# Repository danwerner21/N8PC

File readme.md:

# N8PC
The N8PC is a Z180 ATX format board with 512K RAM, 512K of ROM, that supports RomWBW and is compatible enough with MSX to run many games.  It supports a 82c42 PS2 keyboard controller, a TMS9918 emulator (either Pico9918, F19A or Tang Nano) for 80 column video output, a Ay-3-8910 PSG for sound, a 6242 RTC, ATARI/MSX style Joysticks (2 button supported) and 6 ISAish slots.  This computer is supported by the RomWBW ecosystem with full CP/M OS Support.

Note that 9.218Mhz is the recommended system clock speed for this system.  

## BUGS
```
V1.1 version PCBs have not been tested yet.

Bodges for V1.0 of Board
U33 Cut Pin 3 traces on both Top and Bottom
U33 Cut Pin 5 trace on Bottom

U6 Cut Pin 8 trace on Bottom (NOT TOP!!)

Connect CS_RTC from U47 Pin 2 to U9 Pin 11
Connect U33 Pin 3 To U5 Pin 5
Connect U33 Pin 5 To U5 Pin 6
Connect U18 Pin 2 to U18 Pin 13
```

### Jumper Settings
[TO DO]

### Building the system
[TO DO]

### Default Memory Map
** See RomWBW or C-BIOS Documentation
RomWBW Support: https://github.com/wwarthen/RomWBW
CBIOS MSX Game Support: https://github.com/danwerner21/msxbios

Note that the CBIOS MSX game support is still a work in progress.  It does work, but there is still much work to do. I am not including any actual game ROMS, I leave that to the builder to locate those ROMs as they are easily found on the Internet.

### Bill Of Materials
Reference|Value|Qty|Description
---------|-----|---|-----------
BT1|Battery_Cell|1|CR2032 battery holder
C1-C4,C17|22 uF|5|Polarized capacitor
C5-C8,C10-C13,C15,C16,C18-C27,C29-C33,C36-C41,C43-C54,C56|0.1 uF|44|Unpolarized capacitor
C28|1uF|1|Polarized capacitor
C34|4.7pF|1|
C35|10uF|1|Polarized capacitor
C55,C58,C61-C64,C67,C71-C73|1.0 uF|10|Polarized capacitor, small symbol
C57|0.01 uF|1|Unpolarized capacitor
C59,C60|15pf|2|Unpolarized capacitor
C101,C102|270 pF|2|Unpolarized capacitor
C109,C110|10 uF|2|Polarized capacitor, small symbol
D1,D2|1N4148|2|Diode
D3,D4|D|2|Diode
D5|1N5817|1|20V 1A Schottky Barrier Rectifier Diode, DO-41
D6|RUN/HALT|1|Dual LED, bidirectional
D7|LED1|1|Light emitting diode
D8|LED2|1|Light emitting diode
D9|LED3|1|Light emitting diode
D10|LED0|1|Light emitting diode
D11|IDE|1|Light emitting diode
D12|STATUS|1|Light emitting diode
J1,J2,J5,J7,J9,J13|IRQ Selection|6|Generic connector, double row, 02x06
J3,J4,J6,J8,J10,J14|Bus_ISA_8bit|6|8-bit ISA-PC bus connector
J11|F18A TANG NANO Connector|1|Generic connector, double row, 02x10
J12|FRONT_PANEL|1|Generic connector, double row, 02x11
J15|MOUSE|1|6-pin Mini-DIN connector
J16|KEYBOARD|1|6-pin Mini-DIN connector
J17,J19|TTL SERIAL CONSOLE|2|Generic connector, single row, 01x06
J18,J20|TTL CONSOLE PWR|2|Generic connector, single row, 01x02
J21|KEYBOARD IRQ|1|Generic connector, double row, 02x02
J22|BUS IRQ|1|Generic connector, double row, 02x02
J23|VIDEO IRQ|1|Generic connector, double row, 02x02
JP2|CTS0|1|Jumper, 2-pole, open
JP3|CTS1|1|Jumper, 2-pole, open
JP10|JUMPER|1|Jumper, 2-pole, open
K2|IDE_PWR|1|Generic connector, single row, 01x03
K3-K5,K16,K18|CONN_3|5|Generic connector, single row, 01x03
K17|CPU_CLK|1|Generic connector, single row, 01x03
P1|IO_ADDR|1|Generic connector, double row, 02x03
P11|CONN_10X2|1|Generic connector, double row, 02x10
P12|POWER_SW|1|Generic connector, single row, 01x02
P13,P18|SERIAL|2|Generic connector, double row, 02x05
P14|14.31818 MHz CLK|1|
P15|AUDIO|1|Generic connector, double row, 02x05
P16|IO_ADDR2|1|Generic connector, double row, 02x03
P19|ASCI OSC|1|
P27|FLOPPY|1|Generic connector, double row, 02x17
P29|PPIDE|1|Generic connector, double row, 02x20
P31|PARALLEL EXP|1|Generic connector, double row, 02x13
P37|CPU OSC|1|
P41|OSC_FDC|1|
P43|CHAN_MIX|1|Generic connector, double row, 02x02
P51|JOYSTICK0|1|Generic connector, double row, 02x05
P52|JOYSTICK1|1|Generic connector, double row, 02x05
R1,R3|10k|2|Resistor
R2,R5,R7,R9,R10,R36|470|6|Resistor
R4,R13,R14,R26|4.7K|4|Resistor
R6,R17,R19,R21|1000|4|Resistor
R8,R12,R46,R47,RN5,RR1,RR5,RR8,RV1,RV2|4700|10|9 resistor network, star topology, bussed resistors, small US symbol,Potentiometer,Resistor
R11|100|1|Resistor
R16,R22-R24|10K|4|Resistor
R42|2200|1|Resistor
RP1|150|1|8 resistor network, star topology, bussed resistors, small symbol
SW1|POWER|1|Push button switch, generic, two pins
SW2|RESET|1|Push button switch, generic, two pins
U1,U3,U4,U16,U31|74LS244|5|Octal Buffer and Line Driver With 3-State Output, active-low enables, non-inverting outputs
U2,U63|74LS14|2|Hex inverter schmitt trigger
U5|74LS02|1|quad 2-input NOR gate
U6,U7,U18|74LS32|3|Quad 2-input OR
U8|74LS08|1|Quad And2
U9,U58,U68|74LS138|3|Decoder 3 to 8 active low outputs
U10,U35|MAX232|2|Dual RS232 driver/receiver, 5V supply, 120kb/s, 0C-70C
U12|74LS74|1|Dual D Flip-flop, Set & Reset
U13|27C080|1|OTP EPROM 8 MiBit (1 Mi x 8)
U14|74LS125|1|Quad buffer 3-State outputs
U15|74LS245|1|Octal BUS Transceivers, 3-State outputs
U19|74HCT14|1|Hex inverter schmitt trigger
U21,U57|74LS682N|2|
U23|TMS9918 EMU|1|
U24|CLK|1|
U25|82c42|1|
U26|74LS06|1|
U29|DS1233|1|
U32|74LS139|1|Dual Decoder 1 of 4, Active low outputs
U33|74LS10|1|Triple 3-input NAND
U34|74LS393|1|Dual BCD 4-bit counter
U38|8255|1|Programmable Peripheral Interface, PDIP-40
U39|74LS04|1|Hex Inverter
U47|M6242|1|M6242
U48|AY-3-8910|1|
U49|74LS07N|1|Hex Buffers and Drivers With Open Collector High Voltage Outputs
U51|STEREO_JACK|1|Audio Jack, 3 Poles (Stereo / TRS)
U52|Z8S180|1|
U53|SRAM_512KO|1|512K x 8 Low Power CMOS RAM, DIP-32
U55|74LS273|1|8-bit D Flip-Flop, reset
U61|WD37C65BJM|1|
U66,U67|74LS157|2|Quad 2 to 1 line Multiplexer
U70|74LS174|1|Hex D-type Flip-Flop, reset
X1|RTC_OSC|1|Two pin crystal

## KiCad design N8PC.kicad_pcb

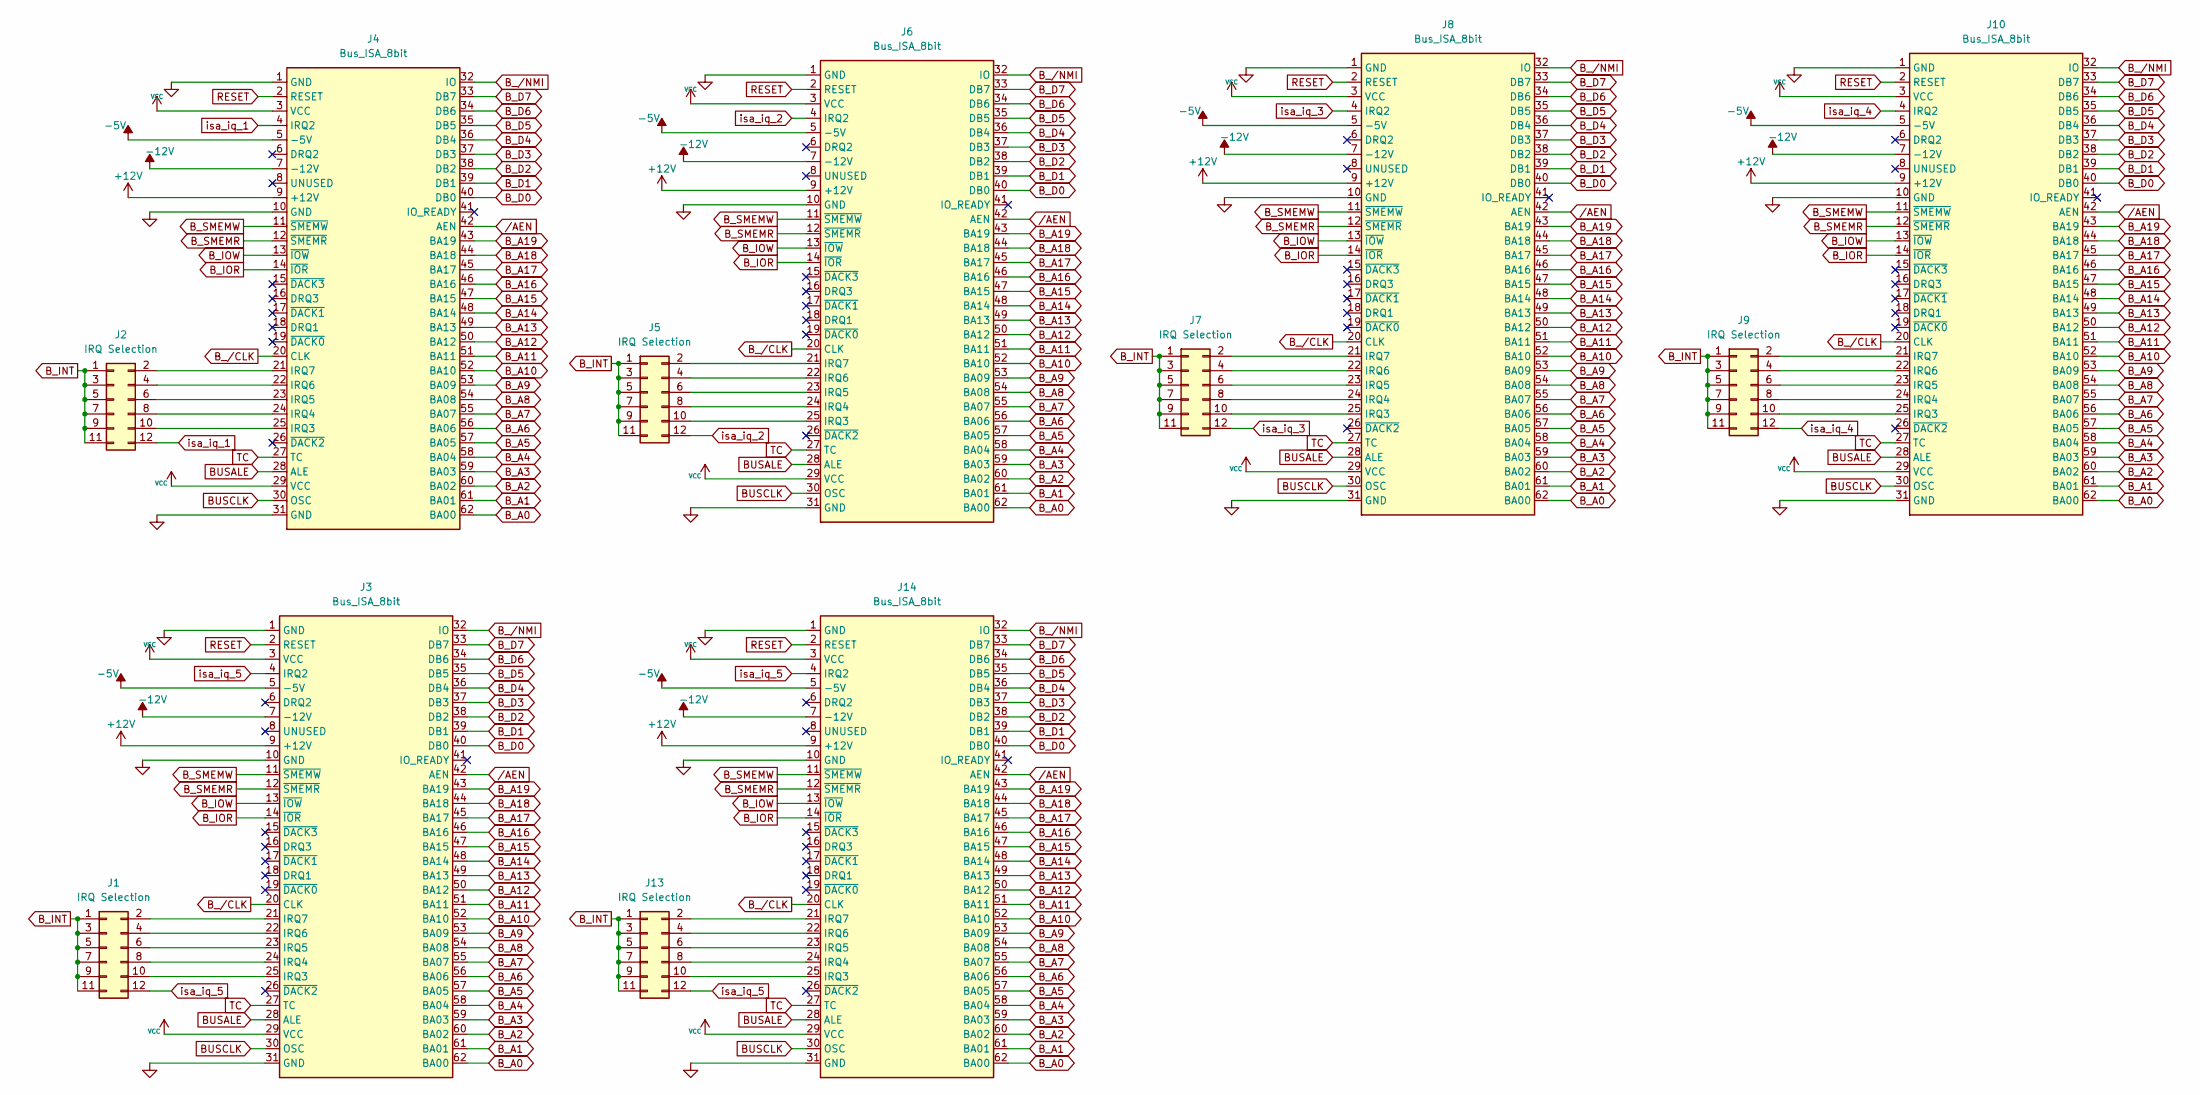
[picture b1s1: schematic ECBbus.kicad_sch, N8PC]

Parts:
J1, J2, J5, J7, J9, J13: IRQ Selection; STD_DDW_PINHEAD_V_2x06
J3, J4, J6, J8, J10, J14: Bus_ISA_8bit; BUSPC_HOST

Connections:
+5V: J3.3 (VCC), J3.29 (VCC), J4.3 (VCC), J4.29 (VCC), J6.3 (VCC), J6.29 (VCC), J8.3 (VCC), J8.29 (VCC), J10.3 (VCC), J10.29 (VCC), J14.3 (VCC), J14.29 (VCC); also elsewhere on the board
+12V: J3.9 (+12V), J4.9 (+12V), J6.9 (+12V), J8.9 (+12V), J10.9 (+12V), J14.9 (+12V); also elsewhere on the board
-5V: J3.5 (-5V), J4.5 (-5V), J6.5 (-5V), J8.5 (-5V), J10.5 (-5V), J14.5 (-5V); also elsewhere on the board
-12V: J3.7 (-12V), J4.7 (-12V), J6.7 (-12V), J8.7 (-12V), J10.7 (-12V), J14.7 (-12V); also elsewhere on the board
BUSALE: J3.28 (ALE), J4.28 (ALE), J6.28 (ALE), J8.28 (ALE), J10.28 (ALE), J14.28 (ALE)
BUSCLK: J3.30 (OSC), J4.30 (OSC), J6.30 (OSC), J8.30 (OSC), J10.30 (OSC), J14.30 (OSC); also elsewhere on the board
B_A0: J3.62 (BA00), J4.62 (BA00), J6.62 (BA00), J8.62 (BA00), J10.62 (BA00), J14.62 (BA00); also elsewhere on the board
B_A1: J3.61 (BA01), J4.61 (BA01), J6.61 (BA01), J8.61 (BA01), J10.61 (BA01), J14.61 (BA01); also elsewhere on the board
B_A2: J3.60 (BA02), J4.60 (BA02), J6.60 (BA02), J8.60 (BA02), J10.60 (BA02), J14.60 (BA02); also elsewhere on the board
B_A3: J3.59 (BA03), J4.59 (BA03), J6.59 (BA03), J8.59 (BA03), J10.59 (BA03), J14.59 (BA03); also elsewhere on the board
B_A4: J3.58 (BA04), J4.58 (BA04), J6.58 (BA04), J8.58 (BA04), J10.58 (BA04), J14.58 (BA04); also elsewhere on the board
B_A5: J3.57 (BA05), J4.57 (BA05), J6.57 (BA05), J8.57 (BA05), J10.57 (BA05), J14.57 (BA05); also elsewhere on the board
B_A6: J3.56 (BA06), J4.56 (BA06), J6.56 (BA06), J8.56 (BA06), J10.56 (BA06), J14.56 (BA06); also elsewhere on the board
B_A7: J3.55 (BA07), J4.55 (BA07), J6.55 (BA07), J8.55 (BA07), J10.55 (BA07), J14.55 (BA07); also elsewhere on the board
B_A8: J3.54 (BA08), J4.54 (BA08), J6.54 (BA08), J8.54 (BA08), J10.54 (BA08), J14.54 (BA08); also elsewhere on the board
B_A9: J3.53 (BA09), J4.53 (BA09), J6.53 (BA09), J8.53 (BA09), J10.53 (BA09), J14.53 (BA09); also elsewhere on the board
B_A10: J3.52 (BA10), J4.52 (BA10), J6.52 (BA10), J8.52 (BA10), J10.52 (BA10), J14.52 (BA10); also elsewhere on the board
B_A11: J3.51 (BA11), J4.51 (BA11), J6.51 (BA11), J8.51 (BA11), J10.51 (BA11), J14.51 (BA11); also elsewhere on the board
B_A12: J3.50 (BA12), J4.50 (BA12), J6.50 (BA12), J8.50 (BA12), J10.50 (BA12), J14.50 (BA12); also elsewhere on the board
B_A13: J3.49 (BA13), J4.49 (BA13), J6.49 (BA13), J8.49 (BA13), J10.49 (BA13), J14.49 (BA13); also elsewhere on the board
B_A14: J3.48 (BA14), J4.48 (BA14), J6.48 (BA14), J8.48 (BA14), J10.48 (BA14), J14.48 (BA14); also elsewhere on the board
B_A15: J3.47 (BA15), J4.47 (BA15), J6.47 (BA15), J8.47 (BA15), J10.47 (BA15), J14.47 (BA15); also elsewhere on the board
B_A16: J3.46 (BA16), J4.46 (BA16), J6.46 (BA16), J8.46 (BA16), J10.46 (BA16), J14.46 (BA16); also elsewhere on the board
B_A17: J3.45 (BA17), J4.45 (BA17), J6.45 (BA17), J8.45 (BA17), J10.45 (BA17), J14.45 (BA17); also elsewhere on the board
B_A18: J3.44 (BA18), J4.44 (BA18), J6.44 (BA18), J8.44 (BA18), J10.44 (BA18), J14.44 (BA18); also elsewhere on the board
B_A19: J3.43 (BA19), J4.43 (BA19), J6.43 (BA19), J8.43 (BA19), J10.43 (BA19), J14.43 (BA19); also elsewhere on the board
B_D0: J3.40 (DB0), J4.40 (DB0), J6.40 (DB0), J8.40 (DB0), J10.40 (DB0), J14.40 (DB0); also elsewhere on the board
B_D1: J3.39 (DB1), J4.39 (DB1), J6.39 (DB1), J8.39 (DB1), J10.39 (DB1), J14.39 (DB1); also elsewhere on the board
B_D2: J3.38 (DB2), J4.38 (DB2), J6.38 (DB2), J8.38 (DB2), J10.38 (DB2), J14.38 (DB2); also elsewhere on the board
B_D3: J3.37 (DB3), J4.37 (DB3), J6.37 (DB3), J8.37 (DB3), J10.37 (DB3), J14.37 (DB3); also elsewhere on the board
B_D4: J3.36 (DB4), J4.36 (DB4), J6.36 (DB4), J8.36 (DB4), J10.36 (DB4), J14.36 (DB4); also elsewhere on the board
B_D5: J3.35 (DB5), J4.35 (DB5), J6.35 (DB5), J8.35 (DB5), J10.35 (DB5), J14.35 (DB5); also elsewhere on the board
B_D6: J3.34 (DB6), J4.34 (DB6), J6.34 (DB6), J8.34 (DB6), J10.34 (DB6), J14.34 (DB6); also elsewhere on the board
B_D7: J3.33 (DB7), J4.33 (DB7), J6.33 (DB7), J8.33 (DB7), J10.33 (DB7), J14.33 (DB7); also elsewhere on the board
B_INT: J1.1, J1.3, J1.5, J1.7, J1.9, J1.11, J2.1, J2.3, J2.5, J2.7, J2.9, J2.11, J5.1, J5.3, J5.5, J5.7, J5.9, J5.11, J7.1, J7.3, J7.5, J7.7, J7.9, J7.11, J9.1, J9.3, J9.5, J9.7, J9.9, J9.11, J13.1, J13.3, J13.5, J13.7, J13.9, J13.11; also elsewhere on the board
B_IOR: J3.14 (~IOR), J4.14 (~IOR), J6.14 (~IOR), J8.14 (~IOR), J10.14 (~IOR), J14.14 (~IOR); also elsewhere on the board
B_IOW: J3.13 (~IOW), J4.13 (~IOW), J6.13 (~IOW), J8.13 (~IOW), J10.13 (~IOW), J14.13 (~IOW); also elsewhere on the board
B_SMEMR: J3.12 (~SMEMR), J4.12 (~SMEMR), J6.12 (~SMEMR), J8.12 (~SMEMR), J10.12 (~SMEMR), J14.12 (~SMEMR); also elsewhere on the board
B_SMEMW: J3.11 (~SMEMW), J4.11 (~SMEMW), J6.11 (~SMEMW), J8.11 (~SMEMW), J10.11 (~SMEMW), J14.11 (~SMEMW); also elsewhere on the board
B_/CLK: J3.20 (CLK), J4.20 (CLK), J6.20 (CLK), J8.20 (CLK), J10.20 (CLK), J14.20 (CLK); also elsewhere on the board
B_/NMI: J3.32 (IO), J4.32 (IO), J6.32 (IO), J8.32 (IO), J10.32 (IO), J14.32 (IO); also elsewhere on the board
GND: J3.1 (GND), J3.10 (GND), J3.31 (GND), J4.1 (GND), J4.10 (GND), J4.31 (GND), J6.1 (GND), J6.10 (GND), J6.31 (GND), J8.1 (GND), J8.10 (GND), J8.31 (GND), J10.1 (GND), J10.10 (GND), J10.31 (GND), J14.1 (GND), J14.10 (GND), J14.31 (GND); also elsewhere on the board
unnamed: J1.2, J3.21 (IRQ7)
unnamed: J1.4, J3.22 (IRQ6)
unnamed: J1.6, J3.23 (IRQ5)
unnamed: J1.8, J3.24 (IRQ4)
unnamed: J1.10, J3.25 (IRQ3)
unnamed: J2.2, J4.21 (IRQ7)
unnamed: J2.4, J4.22 (IRQ6)
unnamed: J2.6, J4.23 (IRQ5)
unnamed: J2.8, J4.24 (IRQ4)
unnamed: J2.10, J4.25 (IRQ3)
unnamed: J5.2, J6.21 (IRQ7)
unnamed: J5.4, J6.22 (IRQ6)
unnamed: J5.6, J6.23 (IRQ5)
unnamed: J5.8, J6.24 (IRQ4)
unnamed: J5.10, J6.25 (IRQ3)
unnamed: J7.2, J8.21 (IRQ7)
unnamed: J7.4, J8.22 (IRQ6)
unnamed: J7.6, J8.23 (IRQ5)
unnamed: J7.8, J8.24 (IRQ4)
unnamed: J7.10, J8.25 (IRQ3)
unnamed: J9.10, J10.25 (IRQ3)
unnamed: J9.8, J10.24 (IRQ4)
unnamed: J9.6, J10.23 (IRQ5)
unnamed: J9.4, J10.22 (IRQ6)
unnamed: J9.2, J10.21 (IRQ7)
unnamed: J13.2, J14.21 (IRQ7)
unnamed: J13.4, J14.22 (IRQ6)
unnamed: J13.6, J14.23 (IRQ5)
unnamed: J13.8, J14.24 (IRQ4)
unnamed: J13.10, J14.25 (IRQ3)
RESET: J3.2 (RESET), J4.2 (RESET), J6.2 (RESET), J8.2 (RESET), J10.2 (RESET), J14.2 (RESET); also elsewhere on the board
TC: J3.27 (TC), J4.27 (TC), J6.27 (TC), J8.27 (TC), J10.27 (TC), J14.27 (TC)
isa_iq_1: J2.12, J4.4 (IRQ2)
isa_iq_2: J5.12, J6.4 (IRQ2)
isa_iq_3: J7.12, J8.4 (IRQ2)
isa_iq_4: J9.12, J10.4 (IRQ2)
isa_iq_5: J1.12, J3.4 (IRQ2), J13.12, J14.4 (IRQ2)
/AEN: J3.42 (AEN), J4.42 (AEN), J6.42 (AEN), J8.42 (AEN), J10.42 (AEN), J14.42 (AEN); also elsewhere on the board

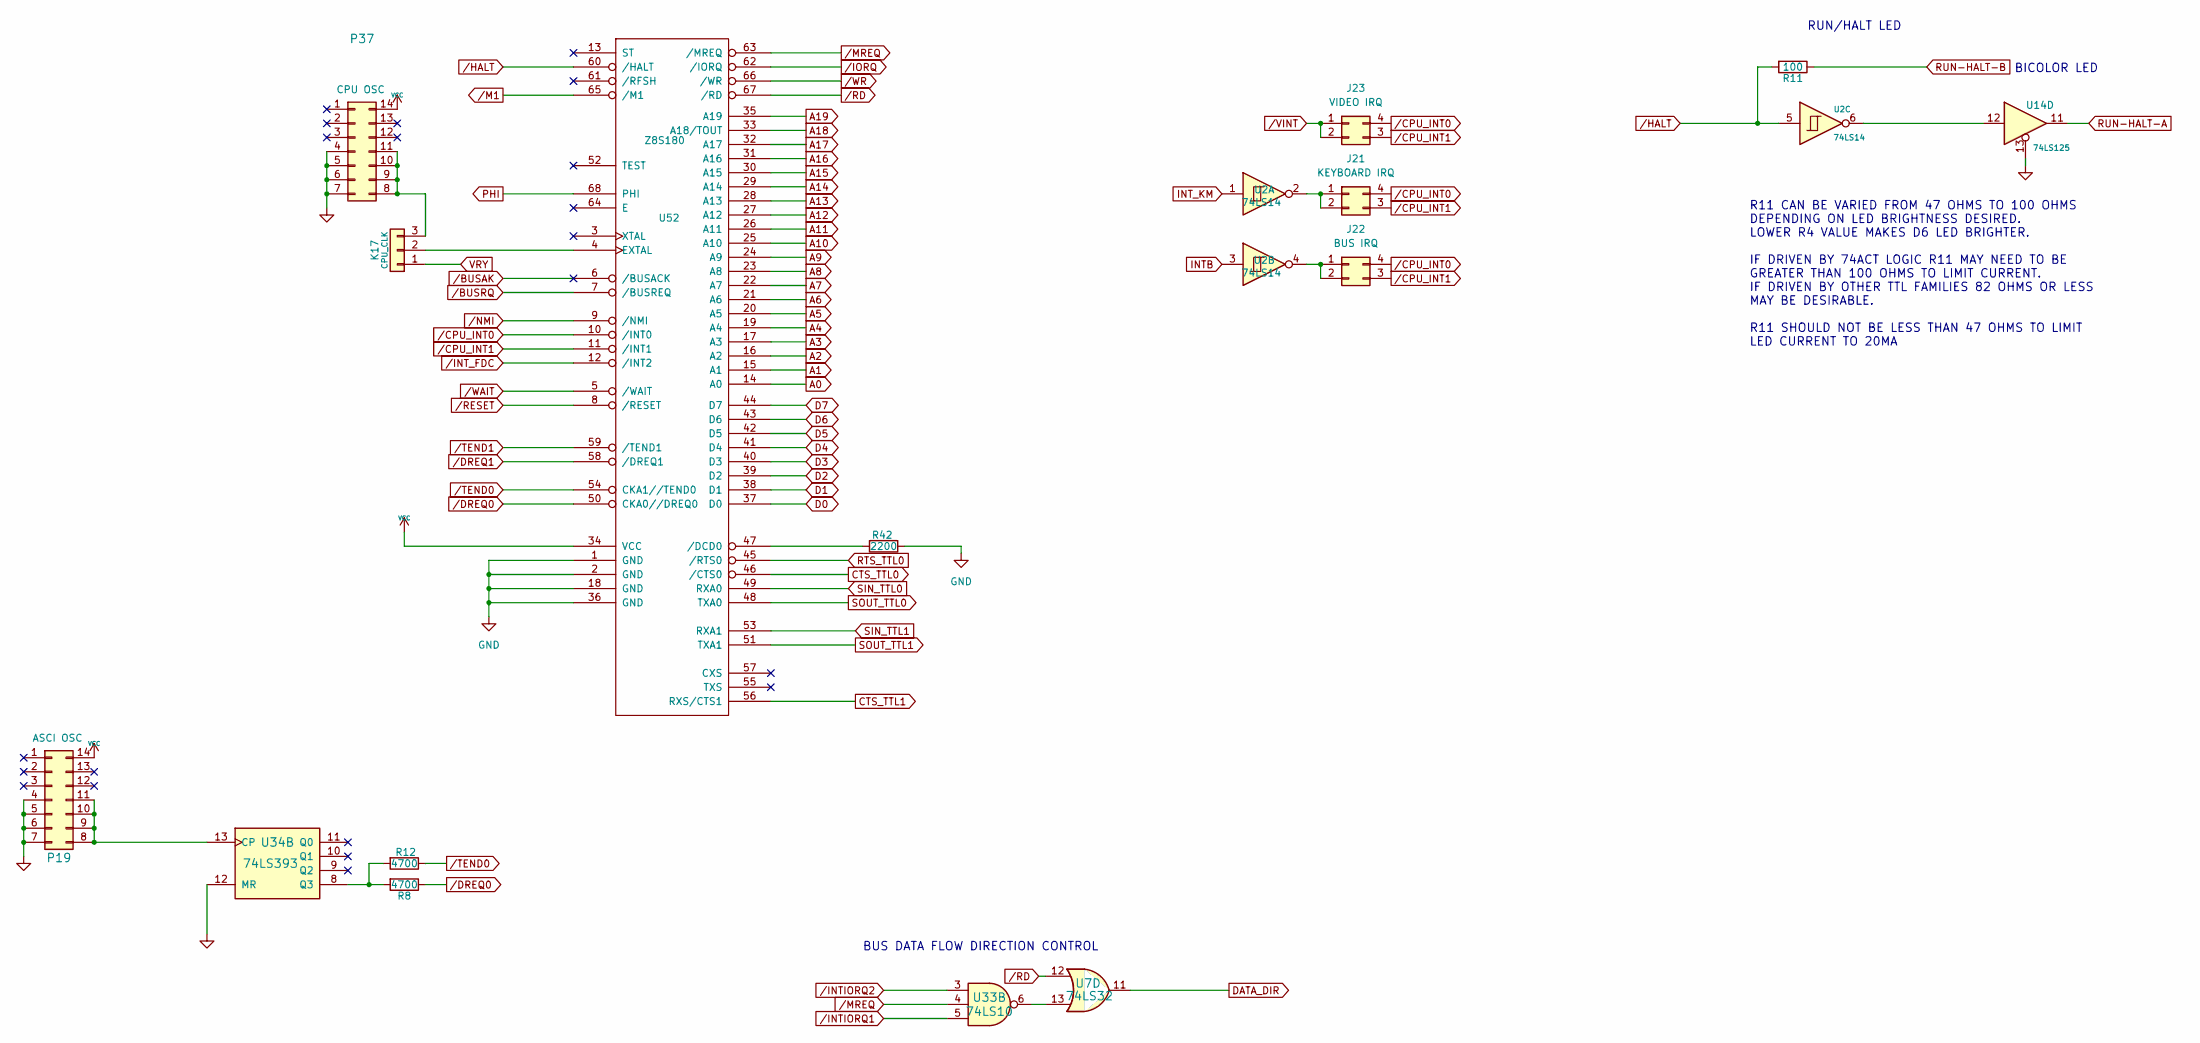
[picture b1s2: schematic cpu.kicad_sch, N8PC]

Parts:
J21: KEYBOARD IRQ; STD_DDW_PinHeader_2x02
J22: BUS IRQ; STD_DDW_PinHeader_2x02
J23: VIDEO IRQ; STD_DDW_PinHeader_2x02
K17: CPU_CLK; STD_DDW_PINHEAD_V_1x03
P19: ASCI OSC; STD_DDW_DIP14
P37: CPU OSC; STD_DDW_DIP14
R8, R12: 4700; STD_DDW_RESISTOR
R11: 100; STD_DDW_RESISTOR
R42: 2200; STD_DDW_RESISTOR
U2: 74LS14; STD_DDW_DIP14
U7: 74LS32; STD_DDW_DIP14
U14: 74LS125; STD_DDW_DIP14
U33: 74LS10; STD_DDW_DIP14
U34: 74LS393; STD_DDW_DIP14
U52: Z8S180; STD_DDW_PLCC-68

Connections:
+5V: P19.14, P37.14, U52.34 (VCC); also elsewhere on the board
A0: U52.14 (A0); also elsewhere on the board
A1: U52.15 (A1); also elsewhere on the board
A2: U52.16 (A2); also elsewhere on the board
A3: U52.17 (A3); also elsewhere on the board
A4: U52.19 (A4); also elsewhere on the board
A5: U52.20 (A5); also elsewhere on the board
A6: U52.21 (A6); also elsewhere on the board
A7: U52.22 (A7); also elsewhere on the board
A8: U52.23 (A8); also elsewhere on the board
A9: U52.24 (A9); also elsewhere on the board
A10: U52.25 (A10); also elsewhere on the board
A11: U52.26 (A11); also elsewhere on the board
A12: U52.27 (A12); also elsewhere on the board
A13: U52.28 (A13); also elsewhere on the board
A14: U52.29 (A14); also elsewhere on the board
A15: U52.30 (A15); also elsewhere on the board
A16: U52.31 (A16); also elsewhere on the board
A17: U52.32 (A17); also elsewhere on the board
A18: U52.33 (A18/TOUT); also elsewhere on the board
A19: U52.35 (A19); also elsewhere on the board
CTS_TTL0: U52.46 (/CTS0); also elsewhere on the board
CTS_TTL1: U52.56 (RXS/CTS1); also elsewhere on the board
D0: U52.37 (D0); also elsewhere on the board
D1: U52.38 (D1); also elsewhere on the board
D2: U52.39 (D2); also elsewhere on the board
D3: U52.40 (D3); also elsewhere on the board
D4: U52.41 (D4); also elsewhere on the board
D5: U52.42 (D5); also elsewhere on the board
D6: U52.43 (D6); also elsewhere on the board
D7: U52.44 (D7); also elsewhere on the board
DATA_DIR: U7.11; also elsewhere on the board
EXT-RES: U52.8 (/RESET); also elsewhere on the board
GND: P19.4, P19.5, P19.6, P19.7, P37.4, P37.5, P37.6, P37.7, R42.1, U14.13, U34.12 (MR), U52.1 (GND), U52.2 (GND), U52.18 (GND), U52.36 (GND); also elsewhere on the board
INTB: U2.3; also elsewhere on the board
INT_KM: U2.1; also elsewhere on the board
unnamed: J21.1, J21.2, U2.2
unnamed: J22.1, J22.2, U2.4
unnamed: K17.2, U52.4 (EXTAL)
unnamed: K17.3, P37.8, P37.9, P37.10, P37.11
unnamed: U2.6, U14.12
unnamed: U7.13, U33.6
unnamed: P19.8, P19.9, P19.10, P19.11, U34.13 (CP)
unnamed: R8.2, R12.2, U34.8 (Q3)
unnamed: R42.2, U52.47 (/DCD0)
PHI: U52.68 (PHI); also elsewhere on the board
RTS_TTL0: U52.45 (/RTS0); also elsewhere on the board
RUN-HALT-A: U14.11; also elsewhere on the board
RUN-HALT-B: R11.1; also elsewhere on the board
SIN_TTL0: U52.49 (RXA0); also elsewhere on the board
SIN_TTL1: U52.53 (RXA1); also elsewhere on the board
SOUT_TTL0: U52.48 (TXA0); also elsewhere on the board
SOUT_TTL1: U52.51 (TXA1); also elsewhere on the board
VRY: K17.1; also elsewhere on the board
/BUSAK: U52.6 (/BUSACK)
/BUSRQ: U52.7 (/BUSREQ); also elsewhere on the board
/CPU_INT0: J21.4, J22.4, J23.4, U52.10 (/INT0); also elsewhere on the board
/CPU_INT1: J21.3, J22.3, J23.3, U52.11 (/INT1); also elsewhere on the board
/DREQ0: R8.1, U52.50 (CKA0//DREQ0)
/DREQ1: U52.58 (/DREQ1); also elsewhere on the board
/HALT: R11.2, U2.5, U52.60 (/HALT)
/INTIORQ1: U33.5; also elsewhere on the board
/INTIORQ2: U33.3; also elsewhere on the board
/INT_FDC: U52.12 (/INT2); also elsewhere on the board
/IORQ: U52.62 (/IORQ); also elsewhere on the board
/M1: U52.65 (/M1); also elsewhere on the board
/MREQ: U33.4, U52.63 (/MREQ); also elsewhere on the board
/NMI: U52.9 (/NMI); also elsewhere on the board
/RD: U7.12, U52.67 (/RD); also elsewhere on the board
/TEND0: R12.1, U52.54 (CKA1//TEND0)
/TEND1: U52.59 (/TEND1); also elsewhere on the board
/VINT: J23.1, J23.2; also elsewhere on the board
/WAIT: U52.5 (/WAIT); also elsewhere on the board
/WR: U52.66 (/WR); also elsewhere on the board

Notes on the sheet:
RUN/HALT LED
BUS DATA FLOW DIRECTION CONTROL
BICOLOR LED
R11 CAN BE VARIED FROM 47 OHMS TO 100 OHMS DEPENDING ON LED BRIGHTNESS DESIRED. LOWER R4 VALUE MAKES D6 LED BRIGHTER. IF DRIVEN BY 74ACT LOGIC R11 MAY NEED TO BE GREATER THAN 100 OHMS TO LIMIT CURRENT. IF DRIVEN BY OTHER TTL FAMILIES 82 OHMS OR LESS MAY BE DESIRABLE. R11 SHOULD NOT BE LESS THAN 47 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

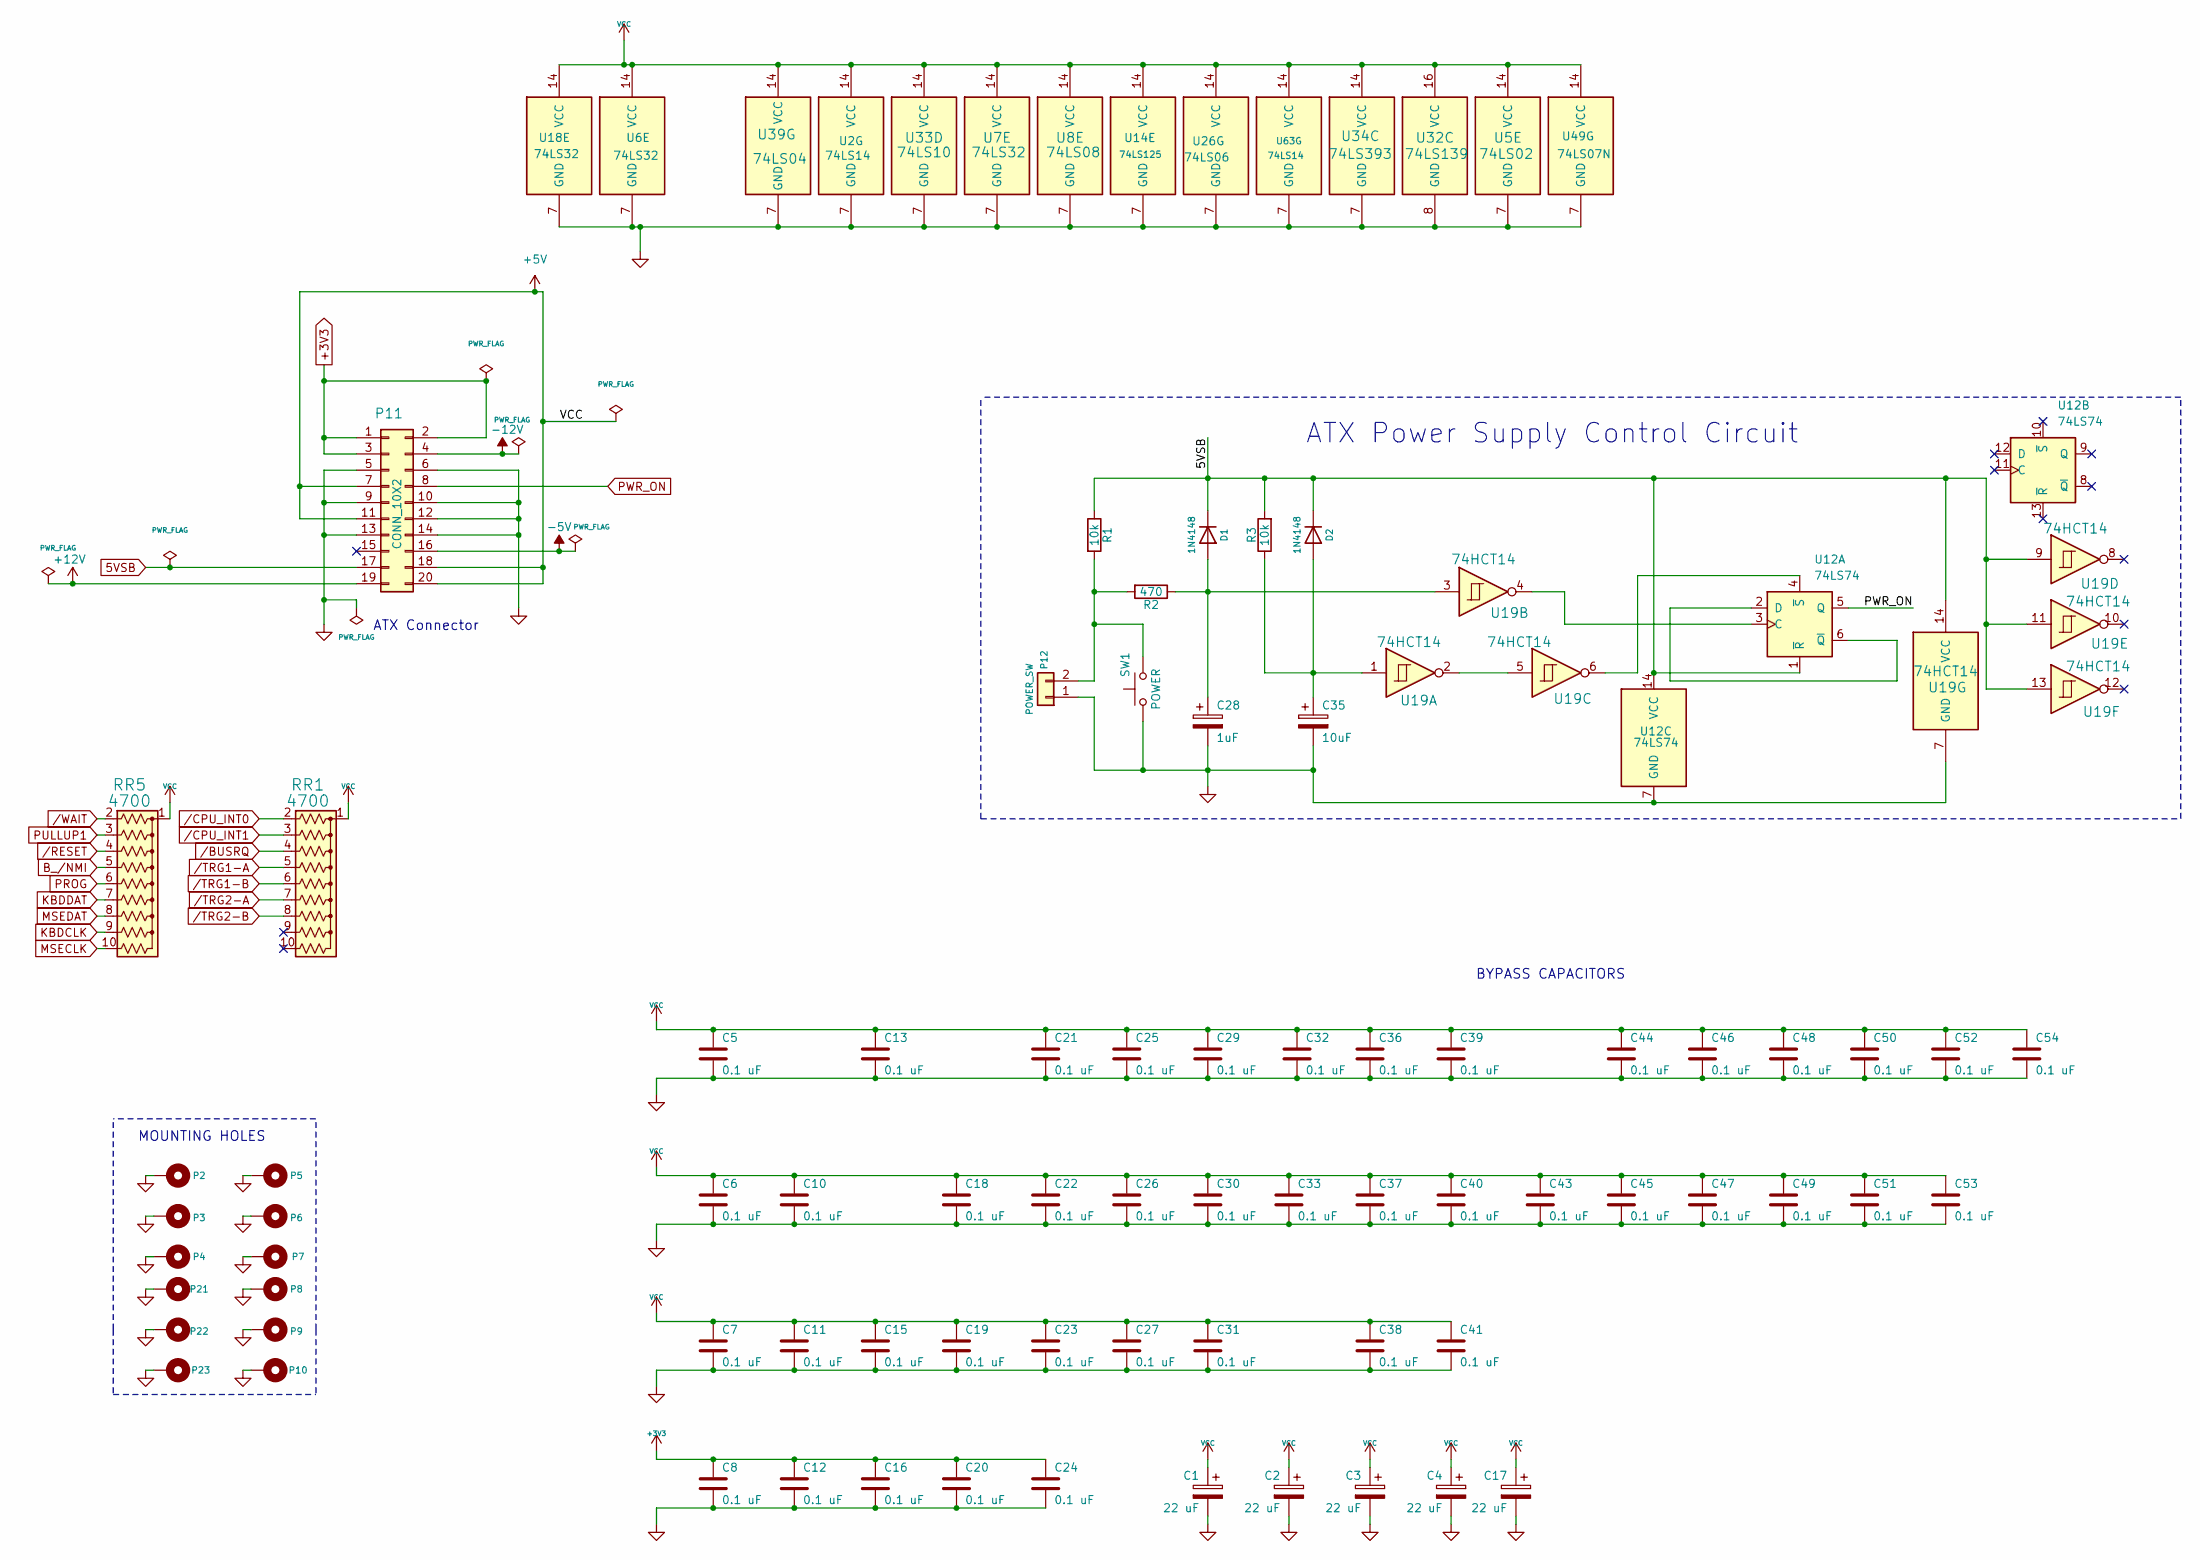
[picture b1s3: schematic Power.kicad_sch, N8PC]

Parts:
C1, C2, C3, C4, C17: 22 uF; STD_DDW_PCAP
C5, C6, C7, C8, C10, C11, C12, C13, C15, C16, C18, C19, C20, C21, C22, C23, C24, C25, C26, C27, C29, C30, C31, C32, C33, C36, C37, C38, C39, C40, C41, C43, C44, C45, C46, C47, C48, C49, C50, C51, C52, C53, C54: 0.1 uF; STD_DDW_CAP
C28: 1uF; STD_DDW_PCAP
C35: 10uF; STD_DDW_PCAP
D1, D2: 1N4148; STD_DDW_DIODE
P2, P3, P4, P5, P6, P7, P8, P9, P10, P21, P22, P23: CONN_1; MountingHole_3.2mm_M3_Pad_TopBottom
P11: CONN_10X2; ATXConnector
P12: POWER_SW; STD_DDW_PINHEAD_V_1x02
R1, R3: 10k; STD_DDW_RESISTOR
R2: 470; STD_DDW_RESISTOR
RR1, RR5: 4700; STD_DDW_SIP10
SW1: POWER; STD_DDW_TACTSW
U2, U63: 74LS14; STD_DDW_DIP14
U5: 74LS02; STD_DDW_DIP14
U6, U7, U18: 74LS32; STD_DDW_DIP14
U8: 74LS08; STD_DDW_DIP14
U12: 74LS74; STD_DDW_DIP14
U14: 74LS125; STD_DDW_DIP14
U19: 74HCT14; STD_DDW_DIP14
U26: 74LS06; STD_DDW_DIP14
U32: 74LS139; STD_DDW_DIP16
U33: 74LS10; STD_DDW_DIP14
U34: 74LS393; STD_DDW_DIP14
U39: 74LS04; STD_DDW_DIP14
U49: 74LS07N; STD_DDW_DIP14

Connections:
5VSB: D1.1 (K), D2.1 (K), P11.17, R1.1, R3.2, U12.1 (~R), U12.14 (VCC), U19.9, U19.11, U19.13, U19.14 (VCC)
+3V3: C8.1, C12.1, C16.1, C20.1, C24.1, P11.1, P11.2, P11.3
+5V: C1.1, C2.1, C3.1, C4.1, C5.1, C6.1, C7.1, C10.1, C11.1, C13.1, C15.1, C17.1, C18.1, C19.1, C21.1, C22.1, C23.1, C25.1, C26.1, C27.1, C29.1, C30.1, C31.1, C32.1, C33.1, C36.1, C37.1, C38.1, C39.1, C40.1, C41.1, C43.1, C44.1, C45.1, C46.1, C47.1, C48.1, C49.1, C50.1, C51.1, C52.1, C53.1, C54.1, P11.7, P11.11, P11.18, P11.20, RR1.1 (common), RR5.1 (common), U2.14 (VCC), U5.14 (VCC), U6.14 (VCC), U7.14 (VCC), U8.14 (VCC), U14.14 (VCC), U18.14 (VCC), U26.14 (VCC), U32.16 (VCC), U33.14 (VCC), U34.14 (VCC), U39.14 (VCC), U49.14 (VCC), U63.14 (VCC); also elsewhere on the board
+12V: P11.19; also elsewhere on the board
-5V: P11.16; also elsewhere on the board
-12V: P11.4; also elsewhere on the board
B_/NMI: RR5.5 (R4); also elsewhere on the board
EXT-RES: RR5.4 (R3); also elsewhere on the board
GND: C1.2, C2.2, C3.2, C4.2, C5.2, C6.2, C7.2, C8.2, C10.2, C11.2, C12.2, C13.2, C15.2, C16.2, C17.2, C18.2, C19.2, C20.2, C21.2, C22.2, C23.2, C24.2, C25.2, C26.2, C27.2, C28.2, C29.2, C30.2, C31.2, C32.2, C33.2, C35.2, C36.2, C37.2, C38.2, C39.2, C40.2, C41.2, C43.2, C44.2, C45.2, C46.2, C47.2, C48.2, C49.2, C50.2, C51.2, C52.2, C53.2, C54.2, P2.1, P3.1, P4.1, P5.1, P6.1, P7.1, P8.1, P9.1, P10.1, P11.5, P11.6, P11.9, P11.10, P11.12, P11.13, P11.14, P12.1, P21.1, P22.1, P23.1, SW1.1, U2.7 (GND), U5.7 (GND), U6.7 (GND), U7.7 (GND), U8.7 (GND), U12.7 (GND), U14.7 (GND), U18.7 (GND), U19.7 (GND), U26.7 (GND), U32.8 (GND), U33.7 (GND), U34.7 (GND), U39.7 (GND), U49.7 (GND), U63.7 (GND); also elsewhere on the board
KBDCLK: RR5.9 (R8); also elsewhere on the board
KBDDAT: RR5.7 (R6); also elsewhere on the board
MSECLK: RR5.10 (R9); also elsewhere on the board
MSEDAT: RR5.8 (R7); also elsewhere on the board
unnamed: C28.1, D1.2 (A), R2.1, U19.3
unnamed: C35.1, D2.2 (A), R3.1, U19.1
unnamed: P12.2, R1.2, R2.2, SW1.2
unnamed: U12.3 (C), U19.4
unnamed: U12.2 (D), U12.6 (~Q)
unnamed: U12.4 (~S), U19.6
unnamed: U19.2, U19.5
PROG: RR5.6 (R5); also elsewhere on the board
PULLUP1: RR5.3 (R2); also elsewhere on the board
PWR_ON: P11.8, U12.5 (Q)
/BUSRQ: RR1.4 (R3); also elsewhere on the board
/CPU_INT0: RR1.2 (R1); also elsewhere on the board
/CPU_INT1: RR1.3 (R2); also elsewhere on the board
/TRG1-A: RR1.5 (R4); also elsewhere on the board
/TRG1-B: RR1.6 (R5); also elsewhere on the board
/TRG2-A: RR1.7 (R6); also elsewhere on the board
/TRG2-B: RR1.8 (R7); also elsewhere on the board
/WAIT: RR5.2 (R1); also elsewhere on the board

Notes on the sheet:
BYPASS CAPACITORS
MOUNTING HOLES
ATX Connector
ATX Power Supply Control Circuit
